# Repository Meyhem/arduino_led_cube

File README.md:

# arduino_led_cube

[Demo video](media/demo.mp4)

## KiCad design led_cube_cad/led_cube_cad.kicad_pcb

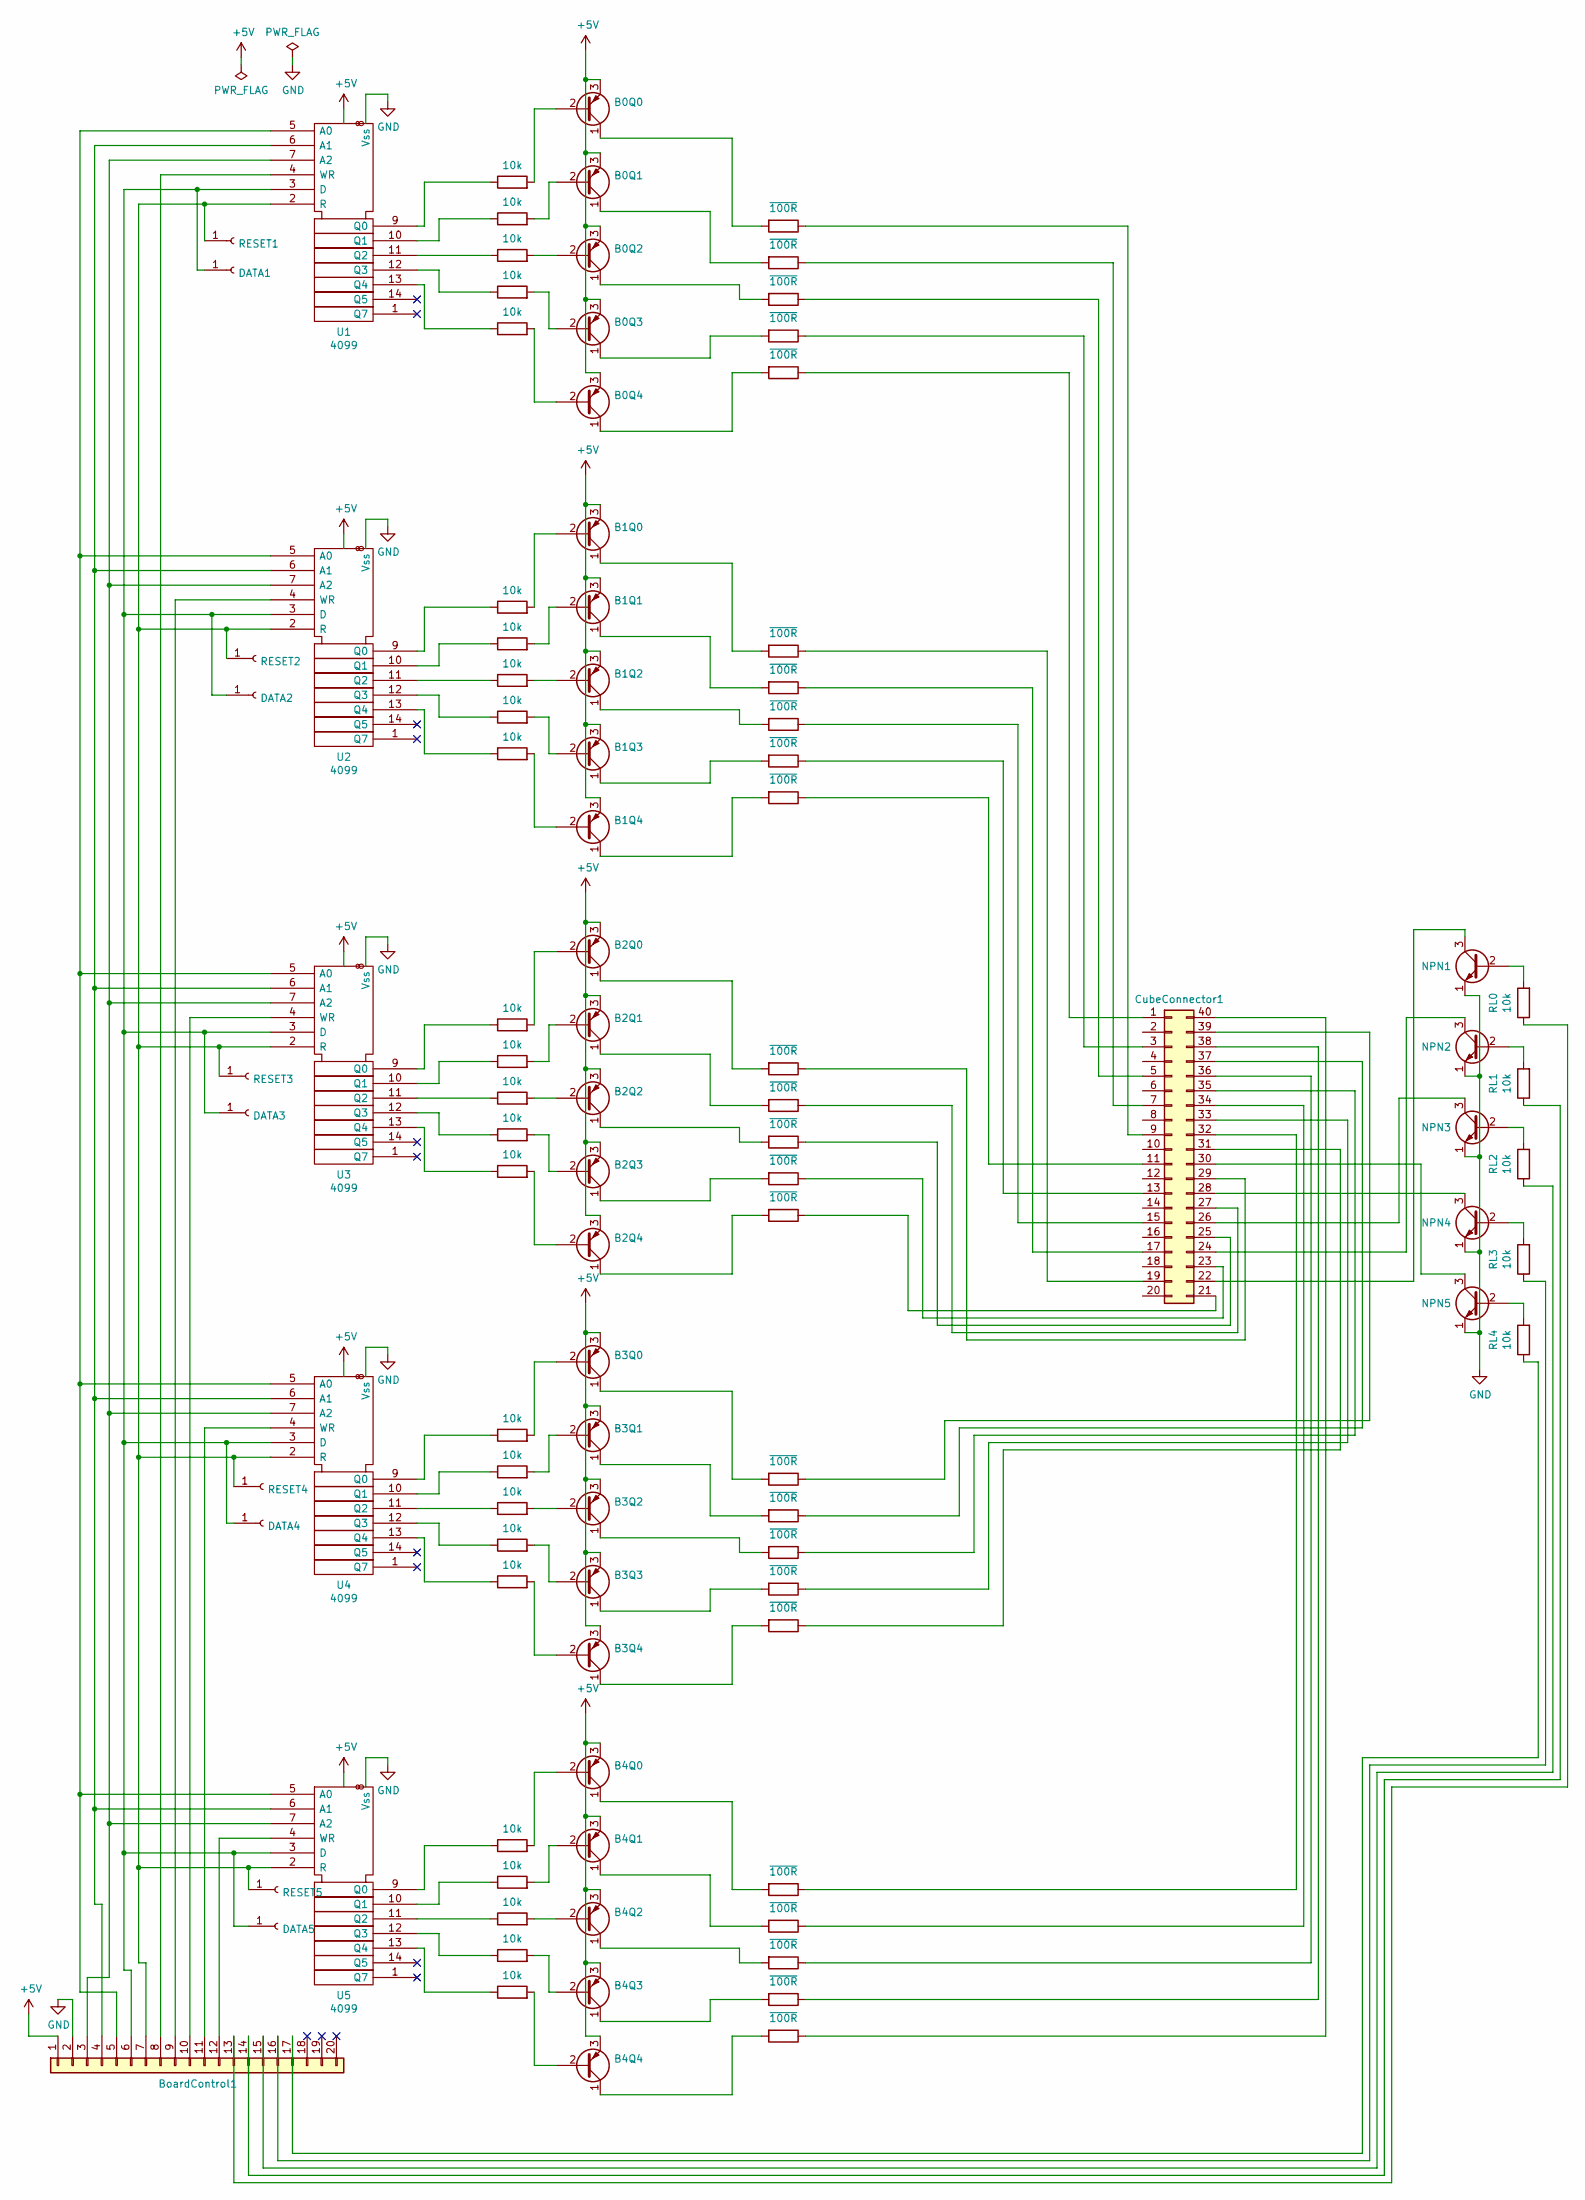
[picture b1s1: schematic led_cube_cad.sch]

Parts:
B0Q0: BC560; TO-92
B0Q1, B0Q2, B0Q3, B0Q4, B1Q0, B1Q1, B1Q2, B1Q3, B1Q4, B2Q0, B2Q1, B2Q2, B2Q3, B2Q4, B3Q0, B3Q1, B3Q2, B3Q3, B3Q4, B4Q0, B4Q1, B4Q2, B4Q3, B4Q4: BC560; TO-92_Inline
BoardControl1: Conn_01x20; PinHeader_1x17_P2.54mm_Vertical
CubeConnector1: Conn_02x20_Counter_Clockwise; PinHeader_2x20_P2.54mm_Vertical
DATA1, DATA2, DATA3, DATA4, DATA5: Conn_01x01_Female; TestPoint_THTPad_D1.5mm_Drill0.7mm
NPN1, NPN2, NPN3, NPN4, NPN5: BC107; TO-18-3
R1, R2, R3, R4, R5, R6, R7, R8, R9, R10, R11, R12, R13, R14, R15, R16, R17, R18, R19, R20, R21, R22, R23, R24, R25: 10k; R_Axial_DIN0309_L9.0mm_D3.2mm_P12.70mm_Horizontal
R26, R27, R28, R29, R30, R31, R32, R33, R34, R35, R36, R37, R38, R39, R40, R41, R42, R43, R44, R45, R46, R47, R48, R49, R50: ~100R; R_Axial_DIN0309_L9.0mm_D3.2mm_P12.70mm_Horizontal
RESET1, RESET2, RESET3, RESET4, RESET5: Conn_01x01_Female; TestPoint_THTPad_D1.5mm_Drill0.7mm
RL0, RL1, RL2, RL3, RL4: 10k; R_Axial_DIN0309_L9.0mm_D3.2mm_P12.70mm_Horizontal
U1, U2, U3, U4, U5: 4099; DIP-16_W10.16mm

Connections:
+5V: B0Q0.3 (E), B0Q1.3 (E), B0Q2.3 (E), B0Q3.3 (E), B0Q4.3 (E), B1Q0.3 (E), B1Q1.3 (E), B1Q2.3 (E), B1Q3.3 (E), B1Q4.3 (E), B2Q0.3 (E), B2Q1.3 (E), B2Q2.3 (E), B2Q3.3 (E), B2Q4.3 (E), B3Q0.3 (E), B3Q1.3 (E), B3Q2.3 (E), B3Q3.3 (E), B3Q4.3 (E), B4Q0.3 (E), B4Q1.3 (E), B4Q2.3 (E), B4Q3.3 (E), B4Q4.3 (E), BoardControl1.1, U1.16 (Vdd), U2.16 (Vdd), U3.16 (Vdd), U4.16 (Vdd), U5.16 (Vdd)
GND: BoardControl1.2, NPN1.1 (E), NPN2.1 (E), NPN3.1 (E), NPN4.1 (E), NPN5.1 (E), U1.8 (Vss), U2.8 (Vss), U3.8 (Vss), U4.8 (Vss), U5.8 (Vss)
unnamed: B0Q0.1 (C), R26.2
unnamed: B0Q0.2 (B), R1.2
unnamed: B0Q1.1 (C), R27.2
unnamed: B0Q1.2 (B), R2.2
unnamed: B0Q2.1 (C), R28.2
unnamed: B0Q2.2 (B), R3.2
unnamed: B0Q3.1 (C), R29.2
unnamed: B0Q3.2 (B), R4.2
unnamed: B0Q4.1 (C), R30.2
unnamed: B0Q4.2 (B), R5.2
unnamed: B1Q0.1 (C), R31.2
unnamed: B1Q0.2 (B), R6.2
unnamed: B1Q1.1 (C), R32.2
unnamed: B1Q1.2 (B), R7.2
unnamed: B1Q2.1 (C), R33.2
unnamed: B1Q2.2 (B), R8.2
unnamed: B1Q3.1 (C), R34.2
unnamed: B1Q3.2 (B), R9.2
unnamed: B1Q4.1 (C), R35.2
unnamed: B1Q4.2 (B), R10.2
unnamed: B2Q0.1 (C), R36.2
unnamed: B2Q0.2 (B), R11.2
unnamed: B2Q1.1 (C), R37.2
unnamed: B2Q1.2 (B), R12.2
unnamed: B2Q2.1 (C), R38.2
unnamed: B2Q2.2 (B), R13.2
unnamed: B2Q3.1 (C), R39.2
unnamed: B2Q3.2 (B), R14.2
unnamed: B2Q4.1 (C), R40.2
unnamed: B2Q4.2 (B), R15.2
unnamed: B3Q0.1 (C), R41.2
unnamed: B3Q0.2 (B), R16.2
unnamed: B3Q1.1 (C), R42.2
unnamed: B3Q1.2 (B), R17.2
unnamed: B3Q2.1 (C), R43.2
unnamed: B3Q2.2 (B), R18.2
unnamed: B3Q3.1 (C), R44.2
unnamed: B3Q3.2 (B), R19.2
unnamed: B3Q4.1 (C), R45.2
unnamed: B3Q4.2 (B), R20.2
unnamed: B4Q0.1 (C), R46.2
unnamed: B4Q0.2 (B), R21.2
unnamed: B4Q1.1 (C), R47.2
unnamed: B4Q1.2 (B), R22.2
unnamed: B4Q2.1 (C), R48.2
unnamed: B4Q2.2 (B), R23.2
unnamed: B4Q3.1 (C), R49.2
unnamed: B4Q3.2 (B), R24.2
unnamed: B4Q4.1 (C), R50.2
unnamed: B4Q4.2 (B), R25.2
unnamed: BoardControl1.3, U1.7 (A2), U2.7 (A2), U3.7 (A2), U4.7 (A2), U5.7 (A2)
unnamed: BoardControl1.4, U1.6 (A1), U2.6 (A1), U3.6 (A1), U4.6 (A1), U5.6 (A1)
unnamed: BoardControl1.5, U1.5 (A0), U2.5 (A0), U3.5 (A0), U4.5 (A0), U5.5 (A0)
unnamed: BoardControl1.6, DATA1.1, DATA2.1, DATA3.1, DATA4.1, DATA5.1, U1.3 (D), U2.3 (D), U3.3 (D), U4.3 (D), U5.3 (D)
unnamed: BoardControl1.7, RESET1.1, RESET2.1, RESET3.1, RESET4.1, RESET5.1, U1.2 (R), U2.2 (R), U3.2 (R), U4.2 (R), U5.2 (R)
unnamed: BoardControl1.8, U1.4 (WR)
unnamed: BoardControl1.9, U2.4 (WR)
unnamed: BoardControl1.10, U3.4 (WR)
unnamed: BoardControl1.11, U4.4 (WR)
unnamed: BoardControl1.12, U5.4 (WR)
unnamed: BoardControl1.13, RL0.1
unnamed: BoardControl1.14, RL1.1
unnamed: BoardControl1.15, RL2.1
unnamed: BoardControl1.16, RL3.1
unnamed: BoardControl1.17, RL4.1
unnamed: CubeConnector1.1, R30.1
unnamed: CubeConnector1.3, R29.1
unnamed: CubeConnector1.5, R28.1
unnamed: CubeConnector1.7, R27.1
unnamed: CubeConnector1.9, R26.1
unnamed: CubeConnector1.11, R35.1
unnamed: CubeConnector1.13, R34.1
unnamed: CubeConnector1.15, R33.1
unnamed: CubeConnector1.17, R32.1
unnamed: CubeConnector1.19, R31.1
unnamed: CubeConnector1.21, R40.1
unnamed: CubeConnector1.22, NPN1.3 (C)
unnamed: CubeConnector1.23, R39.1
unnamed: CubeConnector1.24, NPN2.3 (C)
unnamed: CubeConnector1.25, R38.1
unnamed: CubeConnector1.26, NPN3.3 (C)
unnamed: CubeConnector1.27, R37.1
unnamed: CubeConnector1.28, NPN4.3 (C)
unnamed: CubeConnector1.29, R36.1
unnamed: CubeConnector1.30, NPN5.3 (C)
unnamed: CubeConnector1.31, R45.1
unnamed: CubeConnector1.32, R46.1
unnamed: CubeConnector1.33, R44.1
unnamed: CubeConnector1.34, R47.1
unnamed: CubeConnector1.35, R43.1
unnamed: CubeConnector1.36, R48.1
unnamed: CubeConnector1.37, R42.1
unnamed: CubeConnector1.38, R49.1
unnamed: CubeConnector1.39, R41.1
unnamed: CubeConnector1.40, R50.1
unnamed: NPN1.2 (B), RL0.2
unnamed: NPN2.2 (B), RL1.2
unnamed: NPN3.2 (B), RL2.2
unnamed: NPN4.2 (B), RL3.2
unnamed: NPN5.2 (B), RL4.2
unnamed: R1.1, U1.9 (Q0)
unnamed: R2.1, U1.10 (Q1)
unnamed: R3.1, U1.11 (Q2)
unnamed: R4.1, U1.12 (Q3)
unnamed: R5.1, U1.13 (Q4)
unnamed: R6.1, U2.9 (Q0)
unnamed: R7.1, U2.10 (Q1)
unnamed: R8.1, U2.11 (Q2)
unnamed: R9.1, U2.12 (Q3)
unnamed: R10.1, U2.13 (Q4)
unnamed: R11.1, U3.9 (Q0)
unnamed: R12.1, U3.10 (Q1)
unnamed: R13.1, U3.11 (Q2)
unnamed: R14.1, U3.12 (Q3)
unnamed: R15.1, U3.13 (Q4)
unnamed: R16.1, U4.9 (Q0)
unnamed: R17.1, U4.10 (Q1)
unnamed: R18.1, U4.11 (Q2)
unnamed: R19.1, U4.12 (Q3)
unnamed: R20.1, U4.13 (Q4)
unnamed: R21.1, U5.9 (Q0)
unnamed: R22.1, U5.10 (Q1)
unnamed: R23.1, U5.11 (Q2)
unnamed: R24.1, U5.12 (Q3)
unnamed: R25.1, U5.13 (Q4)

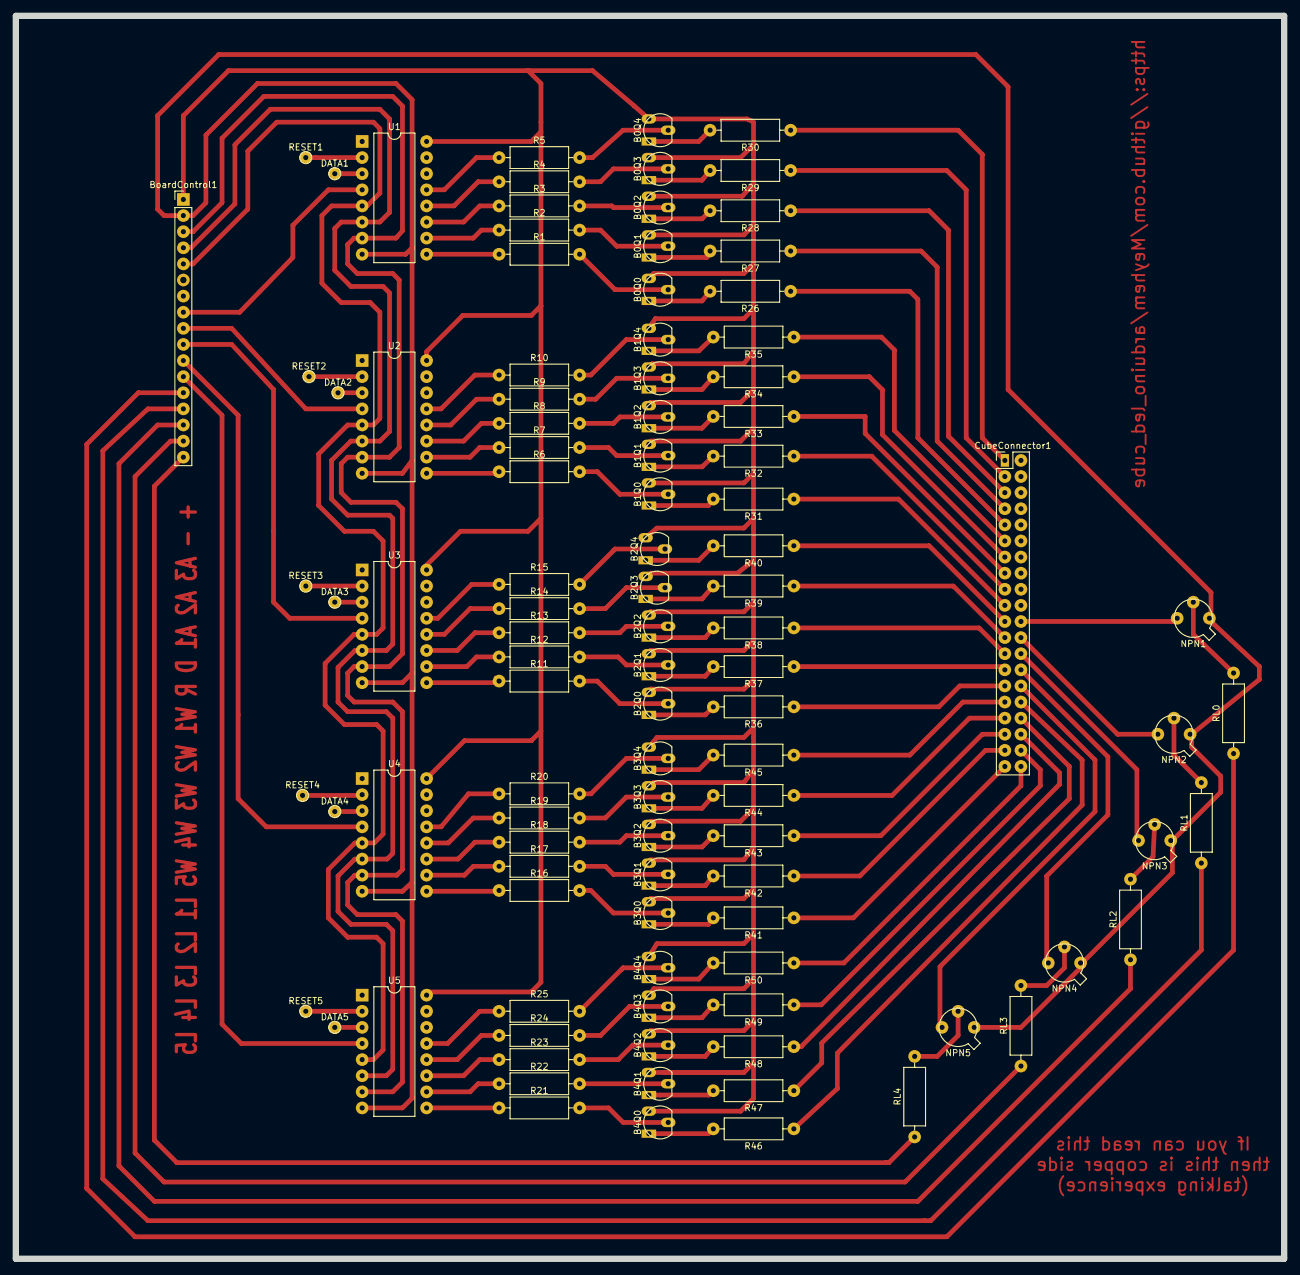
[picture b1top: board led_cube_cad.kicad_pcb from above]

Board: 2 copper layers, 200.0 x 196.0 mm, 102 parts (0 on the bottom side), 127 nets.

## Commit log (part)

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2020-10-25 init
2020-12-05 Functions
2020-12-06 schema
2020-12-06 pcb progress
2020-12-06 some routes
2020-12-06 backup
2020-12-06 track width
2020-12-06 aligning thicks
2020-12-06 addressing wired
2020-12-07 tweaks
2020-12-08 pads
2020-12-08 repositioned layer switches
2020-12-08 edge cuts
2020-12-12 trand pads
2020-12-12 tran pads
2020-12-12 fixes and tweaks
2020-12-12 aligned axes, mount holes
2020-12-12 Drill holes
2020-12-24 funcs
2020-12-24 watever
2021-12-18 nano port
